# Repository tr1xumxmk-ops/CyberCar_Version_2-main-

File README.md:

[SECURE_BACKEND.md](https://github.com/user-attachments/files/33843694/SECURE_BACKEND.md)

<h1 align="center">CYBERCAR SPARK REDLINE</h1>
<p align="center">
  <strong>BLACK · HAZARD YELLOW · SIGNAL RED</strong><br>
  <em>A modular, offline-first Wi-Fi robot car and carrier-PCB engineering project by SPARK Team.</em>
</p>

> **Prototype / safety notice.** This repository contains hobby-grade firmware and a preliminary carrier PCB. The PCB has not been verified by a native KiCad Design Rules Check (DRC) or by physical bench testing in this environment. It is not a production-certified product and should not be fabricated or operated until you complete the verification checklist in this README and `hardware/CyberCar_SPARK_Redline_Carrier/FABRICATION_AND_REVIEW.md`.

## 1. Project at a glance

CyberCar SPARK REDLINE is a small four-wheel chassis controlled by a LOLIN S2 Mini (ESP32-S2). The ESP32 creates its own Wi-Fi access point and serves a locally hosted browser dashboard. A phone joins the car's network and sends commands directly to the ESP32; no home router, cloud service, or Internet uplink is required for this local-control configuration.

The electrical architecture keeps high motor current away from the carrier PCB: an external L298N module drives the motors, while a separate buck converter makes regulated 5 V for the ESP32/accessories. The carrier is an interconnect and accessory board, not a replacement for the ESP32, L298N module, or buck converter.
## Note The Neon_CyberCar is another version with a few changes that can be easily noticed .
like the wifi password and the WebPage Theme&UI also the Servo angle movement .
### Current implementation vs. planned features

| Capability | Status in this release |
|---|---|
| ESP32-created Wi-Fi AP and local captive-portal-style page | Implemented in firmware; phone OS auto-opening varies by device, so `http://192.168.4.1/` can be entered manually. |
| PIN-gated control session | Implemented for the local HTTP dashboard. |
| Manual forward / backward / left / right / stop | Implemented using GPIO direction and enable signals. |
| FAST / MEDIUM / SLOW profiles without ESP32 LEDC hardware PWM | Implemented; MEDIUM/SLOW are timed digital on/off bursts and can feel jerky. |
| Latched emergency-brake command and resume action | Implemented in software; not a safety-rated physical brake. |
| Servo accessory, buzzer and status LEDs | Firmware support is present; verify wiring and optional-library setup. |
| Face images change with robot command/state | Implemented by serving small JPEG files from flash; browser renders them. |
| Native-distance-sensor support | **Not present in this version.** No ultrasonic sensor is included in the firmware or carrier connector plan. |
| Autonomous navigation / trained reinforcement-learning controller | **Not implemented as a driving policy.** UI concepts/art assets are not proof of a trained model. |
| Cloud or public-Internet control | Not implemented. The AP is a local network. |
| Fabrication-ready PCB | Not yet. The Rev-A KiCad source is a reviewable draft; run KiCad DRC and bench checks first. |

## 2. Repository map

```text
CyberCar_SPARK_Redline_Studio/
├── README.md                         Detailed project guide (this file)
├── LICENSE                           Full Apache License 2.0 text for covered software/docs
├── LICENSE-HARDWARE                  Full CERN-OHL-S-2.0 text for covered PCB source
├── LICENSE-HARDWARE-NOTICE.md        Scope/source-location note for the PCB license
├── LICENSE-OVERVIEW.md               How license scopes are separated
├── NOTICE.md                         Attribution, contributor and asset notes
├── LICENSE-IMAGES-AND-ASSETS.md       Notes about photos, faces, fonts and other media
├── SECURE_BACKEND.md                 API validation and security design notes
├── WIRING.md                         Hardware hookup overview
├── HEADER_FILES_GUIDE.md             How the C++ headers are organized
├── FACE_ASSETS_GUIDE.md              Face asset workflow and memory notes
├── BUILD_AND_MEMORY_NOTES.md         Build checklist and flash/RAM guidance
├── CyberCar/CyberCarPro_optimized/
│   ├── CyberCarPro_optimized.ino     Firmware entry point and controller classes
│   ├── config.h                      constexpr hardware/network/time configuration
│   ├── motor_driver.h                GPIO motor driver and drive profiles
│   ├── captive_portal.h              AP, dashboard, HTTP handlers, authentication flow
│   ├── secure_backend.h              Parsing, headers, origin checks, JSON helper
│   └── face_assets.h                 Compressed JPEG bytes stored in flash (PROGMEM)
├── original_uploaded_face_images/    User-supplied source images; check rights before redistributing
├── docs/
│   ├── CyberCar_SPARK_Redline_Preview.html
│   ├── CyberCar_SPARK_Redline_Wiring.png
│   ├── CyberCar_SPARK_Redline_Wiring.svg
│   ├── assets/readme/                Dashboard and controls/team screenshots
│   └── assets/faces/                 Optimized/sample face assets
└── hardware/CyberCar_SPARK_Redline_Carrier/
    ├── CyberCar_SPARK_Redline_Carrier.kicad_pcb   Editable board source
    ├── CyberCar_SPARK_Redline_Carrier.kicad_pro   KiCad project settings
    ├── pcb_layout_preview.png/.svg                 Annotated design preview
    ├── carrier_system_schematic.png/.svg           System wiring explanation (not native KiCad schematic)
    ├── BOM.csv                                     Bill of materials
    ├── CONNECTOR_PINOUT.csv                        Connector map
    ├── README.md                                   PCB-specific instructions
    └── FABRICATION_AND_REVIEW.md                   Pre-fabrication review checklist
```

## 3. Cyberpunk dashboard preview

The live dashboard uses black surfaces, hazard-yellow highlights, and signal-red warning states. It includes a control PIN gate, manual joystick, drive profiles, live state display, face art, auxiliary actions, emergency stop/resume, and SPARK Team cards.

### Dashboard

### Manual controls and SPARK Team

### Run the preview

Open [`docs/CyberCar_SPARK_Redline_Preview.html`](docs/CyberCar_SPARK_Redline_Preview.html) in a desktop or mobile browser. This page is a **local UI simulation**: it does not send commands to the physical car. The actual dashboard is embedded in `captive_portal.h` and served by the ESP32.

The phone's operating system may or may not automatically display a captive-portal prompt. If it does not, join the car's AP and type the address below directly into the browser.

## 4. SPARK Team

| Team member | Role | Discipline |
|---|---|---|
| **Haider Nather** | Team Lead | AI & Robotics Engineering |
| **Ahmed Amjed** | AI Developer | AI & Robotics Engineering |
| **Ayat Sayed** | System Designer | AI & Robotics Engineering |
| **Baraa Fadhel** | Robotics Designer | AI & Robotics Engineering |

### Suggested project ownership

- **Team Lead — Haider Nather:** integration plan, review checklist, release coordination and tracking issues across hardware/software.
- **AI Developer — Ahmed Amjed:** future learning, perception or decision-making experiments; define datasets, baselines and evaluation before claiming an AI feature is operational.
- **System Designer — Ayat Sayed:** interface requirements, subsystem boundaries, dashboard states, API contract and user experience.
- **Robotics Designer — Baraa Fadhel:** chassis, motor/mechanical mounting, wiring harness, PCB fit, component placement and physical test setup.

These assignments are project documentation and may be adjusted by the team. Use only approved photographs/likenesses when adding member profile images. Dashboard labels such as “AI” and “Q-learning” are visual/product organization elements; the current firmware does not include a trained driving policy.

## 5. System architecture

```text
Phone / tablet
  └─ joins Cyber-Car-Pro (local Wi-Fi AP)
      └─ HTTP dashboard at 192.168.4.1
          ├─ authenticated command routes
          └─ status polling
              │
              ▼
       LOLIN S2 Mini / ESP32-S2
          ├─ IN1..IN4: motor direction
          ├─ ENA/ENB: motor-driver enable
          ├─ GPIO13: optional servo signal
          ├─ GPIO18: buzzer driver
          └─ GPIO8 / GPIO9 / GPIO3: R/G/B indicators
              │
              ├─ GPIO harness ──> external L298N logic inputs
              │                    └─ L298N outputs ──> two DC motors
              └─ low-current carrier accessories (LEDs, buzzer, servo rail)
```

This setup is a **local Wi-Fi controller**, not an Internet gateway. A phone may show “Connected without Internet”; that is expected. Do not port-forward the HTTP dashboard to the public Internet.

## 6. Hardware inventory

| Part | Role | Engineering notes |
|---|---|---|
| LOLIN S2 Mini / ESP32-S2 | Wi-Fi AP, HTTP server, command handling and logic GPIO | GPIO is 3.3 V logic; do not apply 5 V to a GPIO. Board pinout must be checked against the exact revision. |
| L298N dual H-bridge module | Reverses motor polarity and enables/disables each motor channel | Motor voltage/current and module regulator/jumpers vary by board; verify your exact module. |
| Two DC gear motors | Drive the chassis | Motor OUT terminals remain on the L298N module, not the carrier PCB. |
| 2S LiPo battery | Supplies motor power and buck input | Nominal 7.4 V, 8.4 V fully charged. Use a suitable balance charger and battery protection practices. |
| 5 V buck converter | Regulated accessory/ESP32 supply | Measure output before connection; set to 5.00 V. Size for servo peak/stall load as well as MCU and accessories. |
| Servo | Optional mechanism | Separate 5 V rail capable of its peak current; share GND with ESP32. Never power servo motor current from a GPIO. |
| R/G/B LEDs with resistors | Visual status | Each LED channel needs its own series resistor. Confirm polarity. |
| Passive piezo buzzer with NPN driver | Audio feedback | Check transistor pin order, resistor values and buzzer polarity/type. |
| Carrier PCB Rev A | Connectorization and low-current accessories | Does not carry motor stall current and has no battery charger/BMS or safety-rated power cut-off. |
| Future expansion connector J5 | Replacement peripheral/sensor interface | No sensor is currently included. GPIO1/GPIO2 are not 5 V tolerant; pick future components accordingly. |

## 7. Wiring reference

- [Editable SVG wiring diagram](docs/CyberCar_SPARK_Redline_Wiring.svg)
- [PCB layout preview](hardware/CyberCar_SPARK_Redline_Carrier/pcb_layout_preview.png)
- [System wiring explanation](hardware/CyberCar_SPARK_Redline_Carrier/carrier_system_schematic.png)
- [CONNECTOR_PINOUT.csv](https://github.com/user-attachments/files/33843589/CONNECTOR_PINOUT.csv)
- [BOM.csv](https://github.com/user-attachments/files/33843893/BOM.csv)

### Critical power rules

1. **Carrier J1 accepts regulated +5.00 V only.** Never connect raw 2S LiPo voltage to J1, the ESP32 5 V/VBUS pin or any GPIO.
2. Route battery positive/negative to the L298N motor supply with suitable wire, connector and fuse/protection. Do not send motor stall current through this carrier board or the ESP32.
3. Connect grounds together: battery negative, buck negative, ESP32 GND, L298N GND, carrier GND and servo GND.
4. On the L298N module, remove the ENA and ENB jumper caps when GPIO11/GPIO12 control the enable inputs.
5. Leave the L298N module's `+5V` terminal disconnected from carrier +5 V unless the documentation for your exact module explicitly requires another connection. L298N boards use different regulator/jumper arrangements.
6. Avoid powering the controller simultaneously from USB and the carrier's +5 V path unless the exact board's power-path isolation has been verified. During early testing, use one supply source at a time.
7. Provide a physical battery disconnect and suitable battery protection. Browser controls, software brake commands and watchdogs are not safety-rated emergency isolation.
8. The future accessory header is 3.3 V logic only. Verify any new replacement component's supply range, IO voltage, current draw, signal timing and common-ground requirements before wiring.

## 8. Pin map (firmware `config.h`)

| ESP32-S2 GPIO | Board/carrier signal | External destination |
|---:|---|---|
| GPIO7 | `MOTOR_IN1_PIN` | L298N IN1 |
| GPIO6 | `MOTOR_IN2_PIN` | L298N IN2 |
| GPIO4 | `MOTOR_IN3_PIN` | L298N IN3 |
| GPIO5 | `MOTOR_IN4_PIN` | L298N IN4 |
| GPIO11 | `MOTOR_ENA_PIN` | L298N ENA; remove ENA jumper |
| GPIO12 | `MOTOR_ENB_PIN` | L298N ENB; remove ENB jumper |
| GPIO13 | `BALL_SERVO_PIN` | Optional servo signal |
| GPIO8 | `LED_RED_PIN` | Red LED through its resistor |
| GPIO9 | `LED_GREEN_PIN` | Green LED through its resistor |
| GPIO3 | `LED_BLUE_PIN` | Blue LED through its resistor |
| GPIO18 | `BUZZER_PIN` | NPN buzzer driver input via resistor |
| GPIO1 | Expansion | Future 3.3 V-safe peripheral only |
| GPIO2 | Expansion | Future 3.3 V-safe peripheral only |

The pin map is also represented in `CONNECTOR_PINOUT.csv`. If you change a GPIO, update `config.h`, the PCB harness table, the wiring illustration, firmware comments and README together.

## 9. Carrier PCB design — Rev A

The included board is an editable **two-layer low-current carrier PCB**. It is meant to simplify wiring and mount accessory circuitry; it does not integrate the ESP32-S2 module, L298N power bridge or the buck converter.

### Files in the KiCad project

| File | Purpose |
|---|---|
| `CyberCar_SPARK_Redline_Carrier.kicad_pcb` | Editable board layout: edge outline, footprints, net names, copper tracks and GND zone definition. |
| `CyberCar_SPARK_Redline_Carrier.kicad_pro` | KiCad project settings. |
| `pcb_layout_preview.svg/.png` | Annotated visual overview for documentation; not Gerber manufacturing output. |
| `carrier_system_schematic.svg/.png` | System-level wiring illustration; **not a native KiCad schematic file**. |
| `BOM.csv` | Proposed component list and notes. |
| `CONNECTOR_PINOUT.csv` | Header/terminal pin map. |
| `FABRICATION_AND_REVIEW.md` | Design-review, safety and fabrication checklist. |

### Preliminary mechanical/electrical assumptions

- Nominal board outline: approximately 110 × 88 mm as marked by `Edge.Cuts`.
- Two copper layers, nominal 1.6 mm FR-4.
- Four M3 mounting-hole positions.
- 5 V and signal interconnects only; no high-current motor power copper on this carrier.
- J1: regulated +5 V/GND input; J2: 1×16 ESP32 harness; J3: 1×7 L298N logic harness; J4: servo; J5: generic 3.3 V accessory expansion; J6: buzzer connector.
- D1–D3 with R3–R5: status LEDs/resistors; Q1/R1/R2: buzzer low-side stage; C1/C2: accessory rail buffering/decoupling.

### Before manufacturing

This is a draft, not a fabricated-and-tested board release. I have not run KiCad DRC in the current environment. In KiCad:

1. Open `CyberCar_SPARK_Redline_Carrier.kicad_pro` or the `.kicad_pcb` file in PCB Editor.
2. Press **B** to refill copper zones.
3. Run **Inspect → Design Rules Checker** and resolve clearance, unconnected, silkscreen and board-outline problems.
4. Inspect both copper layers and confirm each trace meets the correct pad/net. Review the board in 3D view.
5. Verify the real purchased parts match every connector pitch, body outline, pad size, mounting hole and solder clearance.
6. Confirm C1 polarity, Q1 base/collector/emitter lead order, servo pin order and L298N enable-jumper instructions.
7. Check trace widths against your fab's copper thickness, voltage/current and temperature-rise limits.
8. With no power applied, continuity-test +5 V, GND and all signal nets. Then bring up with a current-limited supply and no motors/servo attached.
9. Only after review passes, plot Gerbers and drill files in KiCad and inspect them in an independent Gerber viewer. Gerbers are intentionally not bundled as fabrication-approved outputs.

See the full [FABRICATION_AND_REVIEW.md](https://github.com/user-attachments/files/33843515/FABRICATION_AND_REVIEW.md)
 and [README.md](https://github.com/user-attachments/files/33843531/README.md)

## 10. Firmware layout and header files

The code is split so hardware choices and policies have single sources of truth:

| File | Responsibility |
|---|---|
| `CyberCarPro_optimized.ino` | Setup, watchdog, status LED, sound and servo wrappers, car-controller behavior, main loop. |
| `config.h` | `constexpr` pins, AP credentials, command timeouts, rate limits and drive timing constants. |
| `motor_driver.h` | L298N direction signals, digital enable outputs, drive-level timings and stop/brake states. |
| `captive_portal.h` | Wi-Fi AP, DNS/captive routes, dashboard HTML/CSS/JS, request handlers and session gating. |
| `secure_backend.h` | Security response headers, bounded integer parsing, allowed-value validation, origin check, constant-time PIN compare and JSON escaping helper. |
| `face_assets.h` | JPEG payloads stored in flash (`PROGMEM`) and served to the browser without copying all images into mutable RAM buffers. |

### Why `constexpr` is used

Compile-time settings—pin numbers, timeout values, AP name, speed timing windows, and fixed UI limits—are declared `constexpr` in `config.h`. Current joystick position, session token, active command and emergency-stop state change while the program is running, so they must remain mutable runtime values.

To add a feature, place fixed hardware/settings constants in `config.h`, related reusable behavior in a `.h` module, and keep the main `.ino` focused on integration. Use header guards or `#pragma once`, keep definitions that would cause multiple-definition errors out of headers unless marked appropriately, and update README/pinout/wiring when the interface changes. Read [HEADER_FILES_GUIDE.md](HEADER_FILES_GUIDE.md) before reorganizing files.

## 11. Build and upload

### Requirements

- Arduino IDE 2.x or a compatible Arduino CLI setup.
- Espressif ESP32 board package with an Arduino-ESP32 3.x API compatible with the source.
- Board selection for LOLIN S2 Mini / ESP32-S2 matching the hardware.
- `ESP32Servo` library if the servo-related code is compiled in your local configuration.
- USB data cable, multimeter, suitable battery/buck supply, and access to a physical battery disconnect.

### Steps

1. Extract the project ZIP to a normal writable folder (not inside a ZIP preview).
2. Open `CyberCar/CyberCarPro_optimized/CyberCarPro_optimized.ino` in Arduino IDE.
3. Keep `config.h`, `motor_driver.h`, `secure_backend.h`, `face_assets.h` and `captive_portal.h` in the same sketch directory.
4. Open `config.h`; change the sample AP password and control PIN before public demonstrations. Keep credentials out of public commits.
5. Verify the board selection and USB port; compile and read all diagnostics.
6. Lift the chassis so the wheels are clear. Power the ESP32 through one verified supply path and keep your hand near the physical power switch.
7. Upload. Open Serial Monitor at **115200 baud** if logs are needed.
8. Join the AP and open the dashboard address below. Enter the configured control PIN.
9. Test STOP first, then brief direction commands with wheels raised; test the timeout and emergency latch before floor driving.

### Example local settings in this package

| Setting | Current sample value | Where to edit |
|---|---|---|
| Wi-Fi SSID | `Cyber-Car-Pro` | `config.h` → `Config::AP_SSID` |
| Wi-Fi password | `NeonDrive_2026!` | `config.h` → `Config::AP_PASSWORD` |
| Dashboard URL | `http://192.168.4.1/` | AP configuration / web routes |
| Control PIN | `583104` | `config.h` → `Config::CONTROL_PIN` |

These are sample/default values for project continuity, not unique per-device credentials. Change them before using the car around other people or sharing the firmware.

## 12. Motor control and speed behavior

The current motor driver deliberately avoids ESP32 LEDC hardware-PWM calls. It uses digital GPIO direction signals plus digital enable gating:

- **FAST:** enable pins stay HIGH during commanded movement.
- **MEDIUM:** enable pins are switched on/off in a timed window using `MEDIUM_ON_MS` and `DRIVE_WINDOW_MS`.
- **SLOW:** enable pins are switched on/off using `SLOW_ON_MS` and the same window.
- **STOP:** direction outputs are cleared and enables are disabled.
- **EMERGENCY BRAKE:** software latch switches the H-bridge inputs to the configured braking state and rejects further movement until the resume route is used.

The MEDIUM/SLOW pattern is coarse time-domain switching; it can cause jerking, noise, lower torque or inconsistent movement and it is not a precision speed controller. If smooth low-speed motion matters, use an appropriate motor driver with a PWM input or a properly engineered motor-voltage controller. Never attempt to drive motors directly from ESP32 pins.

A command watchdog/stale-command timeout stops movement when joystick updates stop arriving. The emergency brake is still a software control and is not guaranteed to stop a moving vehicle mechanically under all conditions. Add encoders/current sensing/physical power cutoff as future safety improvements.

## 13. Dashboard/API overview

The actual local API is implemented in `captive_portal.h`. The page uses same-origin requests to the local ESP32 host.

| Route | Method | Purpose | Guardrails |
|---|---|---|---|
| `/` | GET | Serves dashboard HTML | Security response headers; opening the page does not grant control. |
| `/api/login` | POST | Verifies the local control PIN and creates a session cookie | Expected origin, bounded PIN length, constant-time compare, lockout after repeated failures. |
| `/api/state` | GET | Reads current command, level, uptime, memory/status fields | Valid session and rate limit. |
| `/api/joy?x=…&y=…` | POST | Maps bounded joystick coordinates to direction/stop | Valid session, same-origin check, rate limit, x/y range validation. |
| `/api/speed?level=…` | POST | Sets `slow`, `medium`, or `fast` | Allow-listed values, session, origin check, rate limit. |
| `/api/ball?action=…` | POST | Locks or releases servo mechanism | Allow-listed action, session and origin check. |
| `/api/horn` | POST | Plays a short buzzer signal | Session and origin check. |
| `/api/brake` | POST | Latches emergency stop | Session and origin check. |
| `/api/resume` | POST | Clears the latch but leaves the car stopped until another command | Session and origin check. |
| `/assets/faces/*.jpg` | GET | Serves static image bytes from flash | Read-only asset routes; cache headers. |

The joystick is encoded as small bounded integers, not arbitrary JavaScript or executable JSON. The API uses fixed JSON response bodies for most replies; `escapeJsonString()` is a helper for any future dynamic JSON strings. Do not concatenate untrusted input into HTML/JSON, accept arbitrary filenames, or execute received strings.

## 14. Security model and limits

Security improvements are defense-in-depth for a local hobby device; they do not make the device suitable for public exposure.

- **Network boundary:** local ESP32 access point only; no cloud relay is included.
- **PIN gate:** control requires an authentication route; change the sample PIN.
- **Session:** token-based same-origin session cookie with expiry; the browser must preserve the cookie.
- **Input bounds:** joystick coordinates, speed names and accessory actions are range/allow-list checked.
- **Origin checking:** state-changing routes check the expected local origin.
- **Request rate limits:** reduce burst traffic and accidental overload.
- **Response headers:** include common browser hardening headers and a restrictive same-origin policy for the current inline UI.
- **Safe stop:** missing command refreshes trigger a stop; emergency brake is latched.

### Limitations

- Local HTTP is **not encrypted**. Do not route the portal to the public Internet or use it over an untrusted shared network.
- A six-digit PIN has limited entropy; this design is intended for a local prototype. Keep the AP private and change credentials.
- The browser/app model is not a replacement for secure boot, signed updates, physical access control, TLS, or professional penetration testing.
- The current firmware has no obstacle sensing. Add any future sensor only after validating voltage levels, protocol, pin budget, power draw, failure states and wiring.
- Do not claim “JSON injection protection” as a guarantee that all injection is impossible; the code reduces risk by using strict parsing, fixed operations and correct escaping for future dynamic fields.

More information is in [SECURE_BACKEND.md](https://github.com/user-attachments/files/33843496/SECURE_BACKEND.md)

## 15. Face images and memory efficiency

The uploaded face expressions are optimized into compact JPEG assets and embedded in `face_assets.h` in flash memory (`PROGMEM`). Read-only routes serve the JPEG byte arrays directly. The ESP32 does not decode all images into RAM, and the browser chooses the current image state.

The current state map is defined in `captive_portal.h`:

| Situation | Face asset |
|---|---|
| Idle / stopped | `idle.jpg` |
| Forward | `happy.jpg` |
| Reverse | `brake.jpg` (used as a face mood, not a motor-brake command) |
| Left turn | `dance.jpg` |
| Right turn | `drift.jpg` |
| FAST / boost | `dance2.jpg` |
| Emergency latch | `angry.jpg` |
| Error / boot fallback | `boot.jpg` |

To change the art, replace and optimize the images, update the generated byte arrays in `face_assets.h`, and keep the HTTP route names and JS map synchronized. Serve only a single current face in the DOM, choose small dimensions, avoid animated GIF/video, and use CSS transitions for motion in the browser. `PROGMEM` reduces mutable RAM usage but still consumes firmware flash space. Review [FACE_ASSETS_GUIDE.md](FACE_ASSETS_GUIDE.md) and [BUILD_AND_MEMORY_NOTES.md](BUILD_AND_MEMORY_NOTES.md).

The images were supplied in this conversation as project assets. Their ownership/redistribution rights have not been independently verified; see [LICENSE-IMAGES-AND-ASSETS.md](LICENSE-IMAGES-AND-ASSETS.md) before publishing a public repo or reusing imagery.

## 16. Testing and validation checklist

### Power and hardware
- [ ] With power disconnected, check +5 V/GND for shorts and incorrect polarity.
- [ ] Adjust the buck converter and measure 5.00 V before attaching the electronics.
- [ ] Confirm common ground between ESP32, L298N, buck, carrier and servo.
- [ ] Confirm motor battery voltage and peak current requirements match the motor and L298N module.
- [ ] Remove L298N ENA/ENB jumpers when GPIO11/GPIO12 drive the enable inputs.
- [ ] Confirm the exact L298N module's +5 V regulator jumper behavior; do not assume all boards are wired identically.
- [ ] Confirm C1 capacitor polarity, LED orientation, transistor lead order and servo lead order.
- [ ] Check the ESP32 doesn't receive two conflicting 5 V supply paths.

### Firmware/dashboard
- [ ] Compile with the intended Arduino-ESP32 core and required libraries.
- [ ] Verify the AP is visible and the phone stays on it despite the no-Internet indicator.
- [ ] Confirm the dashboard opens at `http://192.168.4.1/` and wrong PIN attempts are rejected.
- [ ] With wheels lifted, issue brief forward/reverse/left/right commands.
- [ ] Confirm release/STOP returns to stopped state.
- [ ] Engage emergency stop; confirm joystick motion remains blocked until explicit resume.
- [ ] Release joystick/stop sending updates and confirm the command timeout stops the wheels.
- [ ] Test FAST/MEDIUM/SLOW on a clear floor with supervision; note jerking and motor temperature.
- [ ] Reset power and verify the car starts in a stopped state.

### PCB
- [ ] Open the PCB in KiCad and refill zones.
- [ ] Run DRC and resolve all warnings/errors before manufacturing.
- [ ] Confirm the board outline and mounting holes fit the intended chassis.
- [ ] Verify the bought header/terminal block footprint and pin order matches the board.
- [ ] Inspect the copper, clearances, silkscreen, solder mask and GND zone connections.
- [ ] Continuity-test every harness pin; check against `CONNECTOR_PINOUT.csv`.
- [ ] Generate Gerbers only after design verification and inspect them in an independent viewer.

## 17. Troubleshooting

| Problem | First checks |
|---|---|
| Wi-Fi network missing | USB power, board boot, serial logs, AP configuration and firmware upload status. |
| Phone says “no Internet” | Normal for a standalone AP. Stay connected and manually open `http://192.168.4.1/`. |
| Portal opens but joystick does nothing | Login session, phone Wi-Fi, AP host address, browser request errors, command rate limits, Serial Monitor output, and motor supply. |
| No motor movement | Battery, L298N motor supply, common ground, enable jumpers, IN/EN wiring, motor outputs and motor terminal fit. |
| One motor runs backward | Swap that motor's two OUT wires or toggle the matching inversion setting after powering down. |
| Medium/slow stutters | Expected from coarse digital ON/OFF bursts; adjust timing cautiously or move to a PWM-capable driver for smooth speed. |
| ESP32 resets when servo moves | Buck peak current, ground/wire resistance, servo jam/stall, bulk capacitance and dual-supply backfeeding. |
| Buzzer silent | Confirm passive buzzer type, Q1 lead order, R1/R2 wiring, supply polarity and GPIO18 assignment. |
| Face picture not showing | Check route name and JavaScript asset map; confirm face arrays/sizes in `face_assets.h`; avoid mismatched file sizes. |
| PCB DRC complains | Refill zones, verify footprints/nets and review `FABRICATION_AND_REVIEW.md`. Do not ignore unconnected-pad or clearance failures. |

## 18. How to make the robot better

Recommended roadmap, from most fundamental to more advanced:

1. **Power integrity:** use protected battery wiring, an accessible disconnect, stable regulated rails and measured motor current.
2. **Mechanical reliability:** secure the battery, strain-relieve motor wires, isolate sharp board corners, and check wheel/motor alignment.
3. **Closed-loop movement:** add wheel encoders and measure speed instead of assuming the commanded power equals a known speed.
4. **Replaceable sensing:** choose a future distance/line/IMU/camera module based on the experiment, then check logic voltage, current, mounting, sampling rate and fail-safe behavior before integration.
5. **Telemetry:** log commanded direction, measured wheel speed, battery voltage (with a properly designed divider/ADC calibration if implemented), resets and command dropouts.
6. **Behavior state machine:** make IDLE, MANUAL, AUTONOMOUS, BRAKE and FAULT explicit states; define which transitions are allowed and what happens after a fault.
7. **AI in a measurable way:** define a task, collect labelled/telemetry data, build a baseline, measure success and failure rates, and only then deploy a model/policy. Do not label UI mock panels as working AI.
8. **PCB Rev B:** after Rev A bench testing, add correctly sized protection, keyed connectors, clear test points, mounting fit checks and (if justified) voltage/current measurement.
9. **Software quality:** use version control, issue tracking, code review for motor/security changes, repeatable compile settings and a short test log for every release.

## 19. Contributing and issue reports

Before sending a patch, include: goal and scope, changed files, compile board/core versions, wiring changes, test conditions, expected behavior, actual behavior and a screenshot/log where useful. Never include personal Wi-Fi passwords or private API secrets in a public issue. Safety-critical changes—motor direction, enable logic, brake, power path or authentication—should receive a second-person review.

## 20. License scope and third-party material

This package intentionally separates software from hardware licensing:

- `LICENSE`: complete Apache License 2.0 text for software/documentation portions that the relevant contributors have authority to license.
- `LICENSE-HARDWARE`: complete unmodified CERN Open Hardware Licence Version 2 — Strongly Reciprocal (`CERN-OHL-S-2.0`) text for the covered carrier PCB source, subject to the scope note in `LICENSE-HARDWARE-NOTICE.md`.
- `LICENSE-OVERVIEW.md` and `NOTICE.md`: scope, attribution and practical redistribution notes.
- `LICENSE-IMAGES-AND-ASSETS.md`: source/face images, team likenesses, logos, icons, fonts and other artwork are not automatically relicensed by the software or hardware licence.
- Third-party libraries and external module designs stay under their own terms.

A license file cannot grant rights the contributors do not own. Before public release or hardware resale, verify authorship, obtain permission from every applicable contributor/rights holder, record a stable source location for the covered PCB design, and check all included photos and artwork. This repository is an educational prototype, not a legal opinion or a safety certification.

## 21. Quick links

- [SECURE_BACKEND.md](https://github.com/user-attachments/files/33843100/SECURE_BACKEND.md)
- [WIRING.md](https://github.com/user-attachments/files/33843136/WIRING.md)
- [HEADER_FILES_GUIDE.md](https://github.com/user-attachments/files/33843170/HEADER_FILES_GUIDE.md)
- [FACE_ASSETS_GUIDE.md](https://github.com/user-attachments/files/33843266/FACE_ASSETS_GUIDE.md)
- [BUILD_AND_MEMORY_NOTES.md](https://github.com/user-attachments/files/33843323/BUILD_AND_MEMORY_NOTES.md)
- [LICENSE-IMAGES-AND-ASSETS.md](https://github.com/user-attachments/files/33843360/LICENSE-IMAGES-AND-ASSETS.md)
- [FABRICATION_AND_REVIEW.md](https://github.com/user-attachments/files/33843394/FABRICATION_AND_REVIEW.md)
- [README.md](https://github.com/user-attachments/files/33843408/README.md)

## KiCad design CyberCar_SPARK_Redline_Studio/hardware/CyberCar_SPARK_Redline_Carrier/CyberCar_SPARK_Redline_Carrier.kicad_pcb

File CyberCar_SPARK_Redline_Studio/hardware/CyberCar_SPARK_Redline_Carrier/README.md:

# CyberCar SPARK REDLINE Carrier PCB — Revision A

**Board class:** two-layer, low-current carrier / interconnect PCB. It is not an integrated ESP32 board, not an L298N H-bridge and not a battery charger. The ESP32-S2, L298N motor-driver module and buck converter remain separate modules connected through headers/wires.

> **Fabrication status: ENGINEERING DRAFT.** The PCB has not been checked with KiCad's native DRC or physically validated in this environment. Do not treat the preview as a manufacturing approval. Review footprints, copper zones, clearances, nets, part pinouts and power paths before plotting Gerbers.

## Files

| File | Use |
|---|---|
| `CyberCar_SPARK_Redline_Carrier.kicad_pcb` | Editable KiCad PCB board source. |
| `CyberCar_SPARK_Redline_Carrier.kicad_pro` | KiCad project settings. |
| `pcb_layout_preview.png` / `.svg` | Annotated visual preview; not a substitute for PCB Editor. |
| `carrier_system_schematic.png` / `.svg` | System wiring explanation, not a native KiCad schematic. |
| `BOM.csv` | Proposed bill of materials. Check actual component datasheets/vendor footprints before ordering. |
| `CONNECTOR_PINOUT.csv` | Connector/pinout source of truth to keep aligned with firmware. |
| `FABRICATION_AND_REVIEW.md` | DRC, electrical, mechanical and manufacturing checklist. |

## Concept and architecture

- Approximate outline: 110 × 88 mm (verify the Edge.Cuts layer in KiCad).
- Two copper layers; nominal 1.6 mm FR-4 assumed.
- Four M3 mounting holes.
- Carrier J1 takes **regulated +5.00 V only** from the buck converter.
- J2 is a 1×16 harness for the LOLIN S2 Mini signals and power.
- J3 is a 1×7 L298N control harness: GND, IN1–IN4, ENA, ENB. It carries logic/control signals only; motor current does not pass through this board.
- J4 is GND/+5 V/servo signal.
- J5 is a 3.3 V/GND/GPIO1/GPIO2 low-current expansion header for a future compatible peripheral.
- J6 is the passive buzzer connector; Q1 drives the low side.
- D1–D3/R3–R5 are status LED channels; C1 and C2 provide accessory-rail buffering/decoupling.

No distance sensor is placed on the carrier or used by this firmware. J5 is generic and is not preconfigured for any specific future sensor.

## Connector/power notes

1. Do not feed battery voltage into J1. It is not a raw battery connector.
2. Route 2S LiPo motor power directly to the L298N's motor supply with appropriately rated wiring/protection. Keep motor stall current off this carrier PCB.
3. Maintain common ground across the battery negative, buck converter, ESP32, carrier, L298N and servo.
4. Remove ENA/ENB jumper caps from the L298N module when GPIO11/GPIO12 drive enable pins. Module implementations differ; inspect the actual board.
5. Leave the L298N module's +5V terminal disconnected from carrier +5V unless the exact module documentation instructs otherwise.
6. Avoid simultaneous USB and carrier power until power-path/backfeed behavior for the actual LOLIN board has been checked.
7. Check the servo's peak/stall current against the buck converter. A servo can cause voltage dips or ESP32 resets if the supply is undersized.
8. J5/GPIOs are 3.3 V only. Add level shifting and power conditioning as required by any future add-on.

## Review in KiCad

1. Open `CyberCar_SPARK_Redline_Carrier.kicad_pro` (or the `.kicad_pcb` board) in KiCad PCB Editor.
2. Press **B** to refill the copper zones.
3. Run **Inspect → Design Rules Checker**. Review and resolve all unconnected pads, clearance errors, board-edge issues, silkscreen overlaps and unconnected copper islands.
4. Inspect F.Cu and B.Cu separately, compare every route to the nets/pads, and view the PCB in 3D.
5. Verify the vendor footprints for terminal blocks, pin headers, resistors, LEDs, transistor and capacitors.
6. Check Q1's actual base/collector/emitter order against its datasheet; TO-92 pin order varies by part/vendor.
7. Check C1 polarity, voltage rating and pitch; check servo signal/GND/+5 V order against the servo data sheet.
8. Verify mounting-hole locations against the real chassis and component clearances against the installed modules.
9. Confirm track widths, clearances and copper requirements with your board manufacturer.
10. With power absent, measure continuity and ensure no short between +5 V and GND. First power on from a current-limited 5 V bench supply if available.
11. Only after all checks pass should you plot Gerber and drill files. Review those plotted files in an independent Gerber viewer before ordering.

## Limits / excluded circuits

This board does not include a charger/BMS, fuse, reverse-polarity protection, motor current measurement, voltage monitoring, overcurrent shutdown, power MOSFET or a safety-rated emergency disconnect. It does not route L298N motor outputs. These functions require a separate validated design and appropriate component sizing.

See the project root `README.md`, `WIRING.md`, `LICENSE-HARDWARE-NOTICE.md` and `FABRICATION_AND_REVIEW.md` for the full system context.

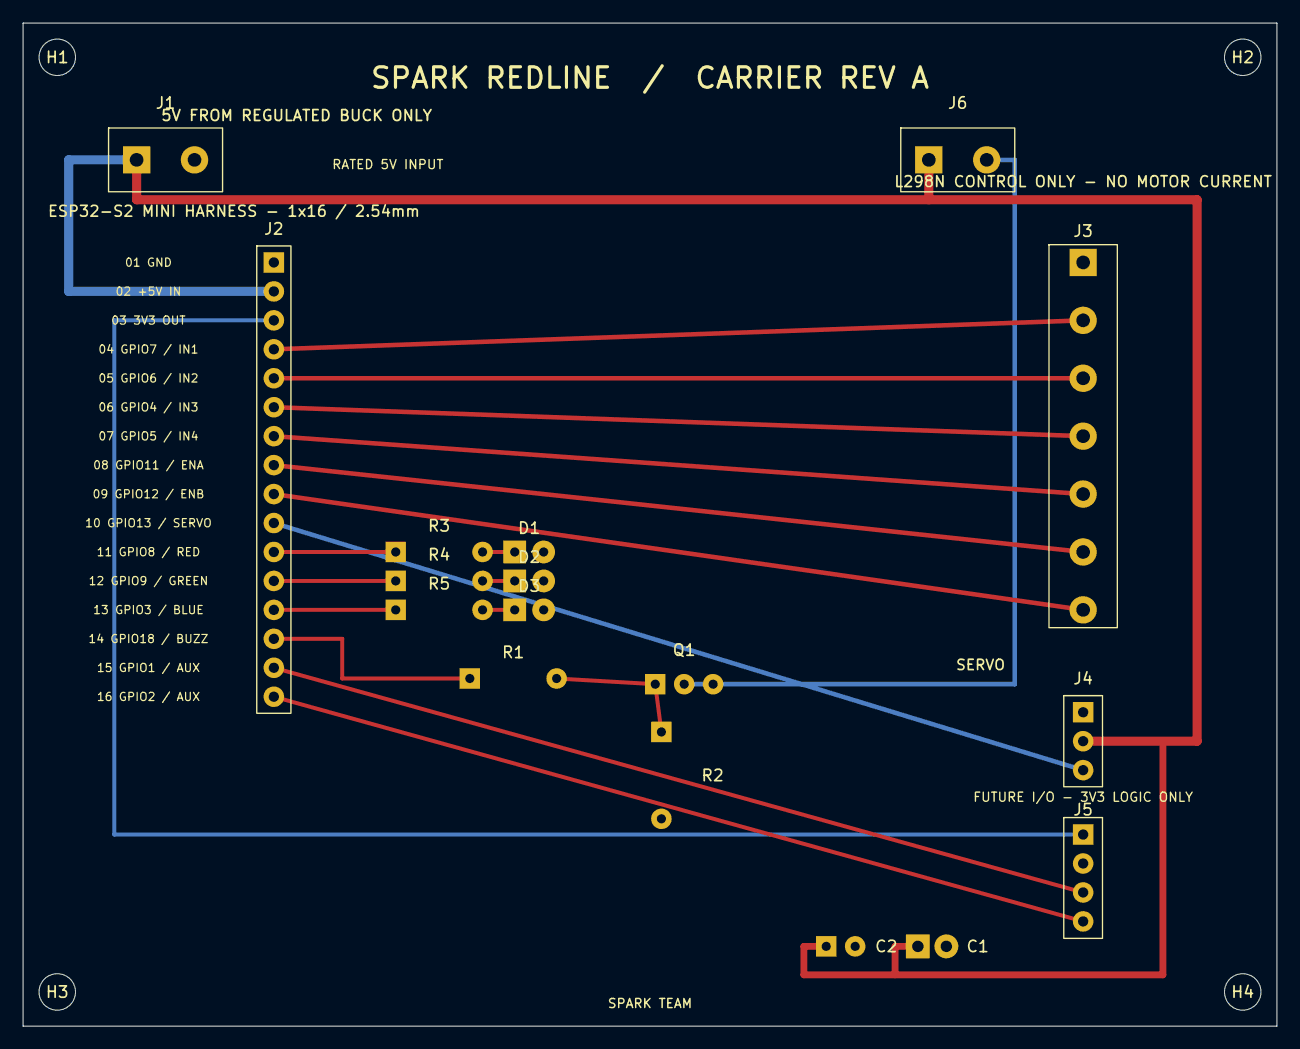
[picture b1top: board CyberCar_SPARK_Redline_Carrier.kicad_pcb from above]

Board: 2 copper layers, 110.0 x 88.0 mm, 21 parts (0 on the bottom side), 21 nets.

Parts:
C1: 470uF_10V; Capacitor_Radial_P2.5mm
C2: 100nF; Capacitor_THT_P2.54mm
D1: LED_RED; LED_THT_P2.54mm
D2: LED_GREEN; LED_THT_P2.54mm
D3: LED_BLUE; LED_THT_P2.54mm
H1, H2, H3, H4: M3_MOUNT; MountingHole_3.2mm
J1: BUCK_5V_IN; TerminalBlock_1x02_P5.08mm
J2: ESP32_SIGNAL_HARNESS; PinHeader_1x16_P2.54mm
J3: L298N_CONTROL_ONLY; TerminalBlock_1x07_P5.08mm
J4: SERVO_5V_SIGNAL; PinHeader_1x03_P2.54mm
J5: FUTURE_IO_3V3; PinHeader_1x04_P2.54mm
J6: PASSIVE_BUZZER; TerminalBlock_1x02_P5.08mm
Q1: NPN_BUZZER_DRIVER; TO92_BCE_VerifyPinout
R1: 1K_BASE; Resistor_Axial_P7.62mm
R2: 10K_BASE_PULLDOWN; Resistor_Axial_P7.62mm
R3: 220R_RED; Resistor_Axial_P7.62mm
R4: 220R_GREEN; Resistor_Axial_P7.62mm
R5: 220R_BLUE; Resistor_Axial_P7.62mm

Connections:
+3V3: J2.3, J5.1
+5V: C1.1, C2.1, J1.1, J2.2, J4.2, J6.1
BUZZER_BASE: Q1.1, R1.2, R2.1
BUZZER_SWITCH: J6.2, Q1.2
GND: C1.2, C2.2, D1.2, D2.2, D3.2, J1.2, J2.1, J3.1, J4.1, J5.2, Q1.3, R2.2
GPIO1_AUX: J2.15, J5.3
GPIO2_AUX: J2.16, J5.4
GPIO3_LED_BLUE: J2.13, R5.1
GPIO4_IN3: J2.6, J3.4
GPIO5_IN4: J2.7, J3.5
GPIO6_IN2: J2.5, J3.3
GPIO7_IN1: J2.4, J3.2
GPIO8_LED_RED: J2.11, R3.1
GPIO9_LED_GREEN: J2.12, R4.1
GPIO11_ENA: J2.8, J3.6
GPIO12_ENB: J2.9, J3.7
GPIO13_SERVO: J2.10, J4.3
GPIO18_BUZZER: J2.14, R1.1
LED_BLUE_A: D3.1, R5.2
LED_GREEN_A: D2.1, R4.2
LED_RED_A: D1.1, R3.2

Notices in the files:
README.md:
Hardware license
